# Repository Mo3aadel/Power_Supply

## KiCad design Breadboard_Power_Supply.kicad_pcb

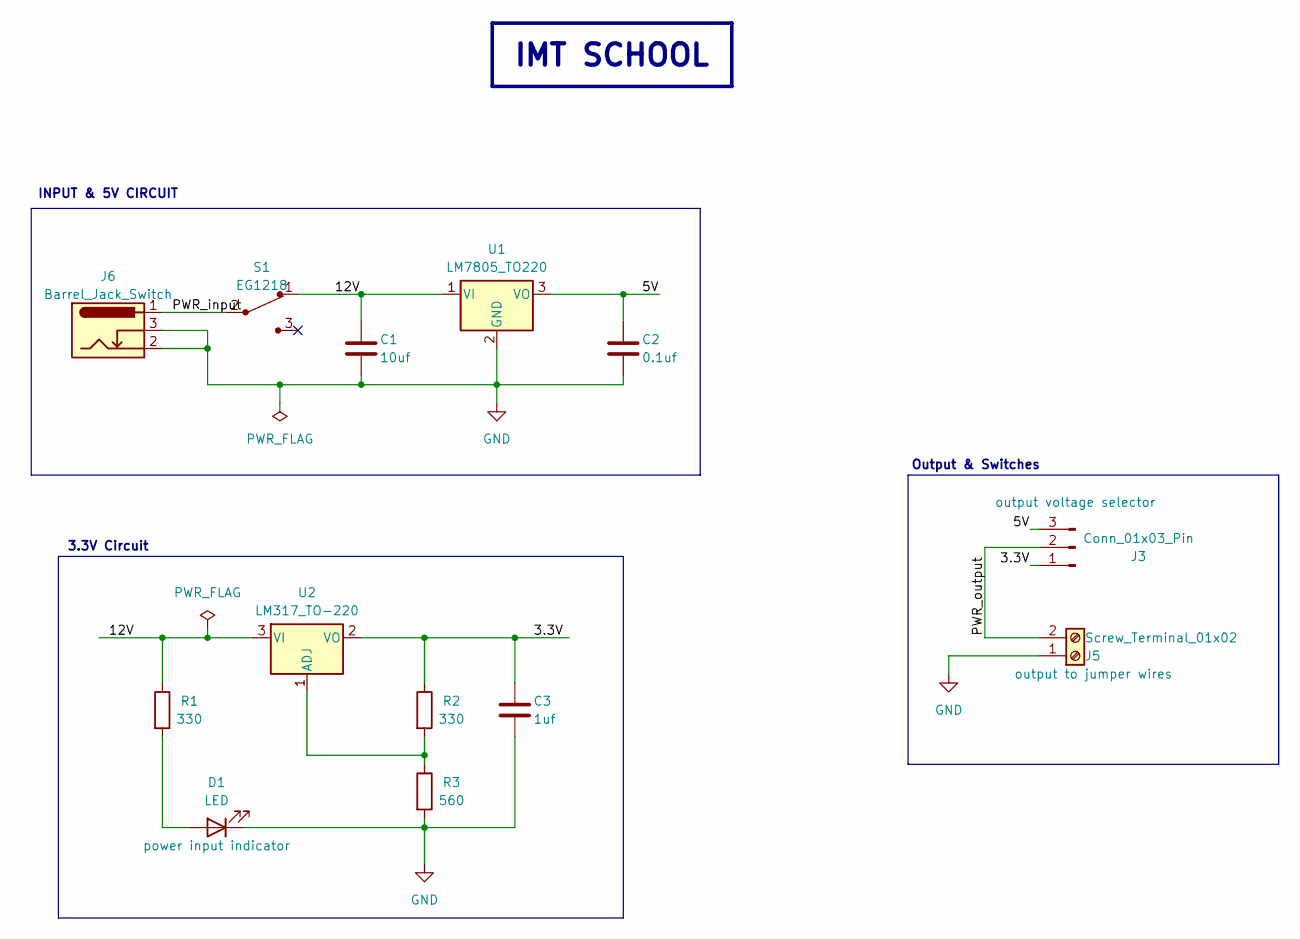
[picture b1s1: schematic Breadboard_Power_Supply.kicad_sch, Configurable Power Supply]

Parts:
C1: 10uf; C_Disc_D3.0mm_W1.6mm_P2.50mm
C2: 0.1uf; C_Disc_D3.0mm_W1.6mm_P2.50mm
C3: 1uf; C_Disc_D3.0mm_W1.6mm_P2.50mm
D1: LED; LED_D5.0mm
J3: Conn_01x03_Pin; PinHeader_1x03_P2.54mm_Vertical
J5: Screw_Terminal_01x02; TerminalBlock_Phoenix_MKDS-1,5-2_1x02_P5.00mm_Horizontal
J6: Barrel_Jack_Switch; BarrelJack_Horizontal
R1, R2: 330; R_Axial_DIN0204_L3.6mm_D1.6mm_P7.62mm_Horizontal
R3: 560; R_Axial_DIN0204_L3.6mm_D1.6mm_P7.62mm_Horizontal
S1: EG1218; Switch_Slide_11.6x4mm_EG1218; MPN EG1218; Digi-Key_PN EG1903-ND
U1: LM7805_TO220; TO-220-3_Vertical
U2: LM317_TO-220; TO-220-3_Vertical

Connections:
/3.3V: C3.1, J3.1, R2.1, U2.2 (VO)
/5V: C2.1, J3.3, U1.3 (VO)
/12V: C1.1, R1.1, S1.1, U1.1 (VI), U2.3 (VI)
/PWR_input: J6.1, S1.2
/PWR_output: J3.2, J5.2
GND: C1.2, C2.2, C3.2, D1.1 (K), J5.1, J6.2, J6.3, R3.2, U1.2 (GND)
unnamed: D1.2 (A), R1.2
unnamed: R2.2, R3.1, U2.1 (ADJ)

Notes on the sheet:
IMT SCHOOL
INPUT & 5V CIRCUIT
3.3V Circuit
Output & Switches

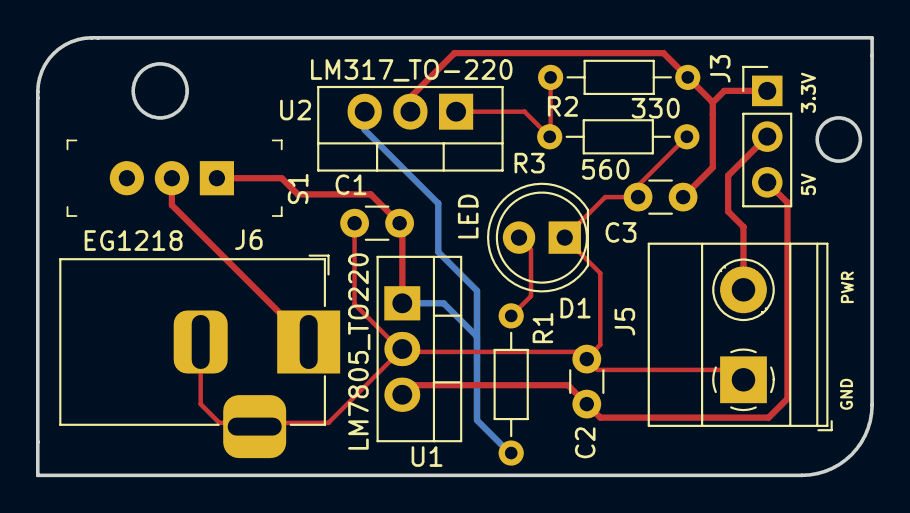
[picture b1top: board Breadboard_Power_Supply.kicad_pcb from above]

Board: 2 copper layers, 46.3 x 24.3 mm, 13 parts (0 on the bottom side), 8 nets.

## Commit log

2024-12-27 the first commit
2024-12-27 Updated the Logo
